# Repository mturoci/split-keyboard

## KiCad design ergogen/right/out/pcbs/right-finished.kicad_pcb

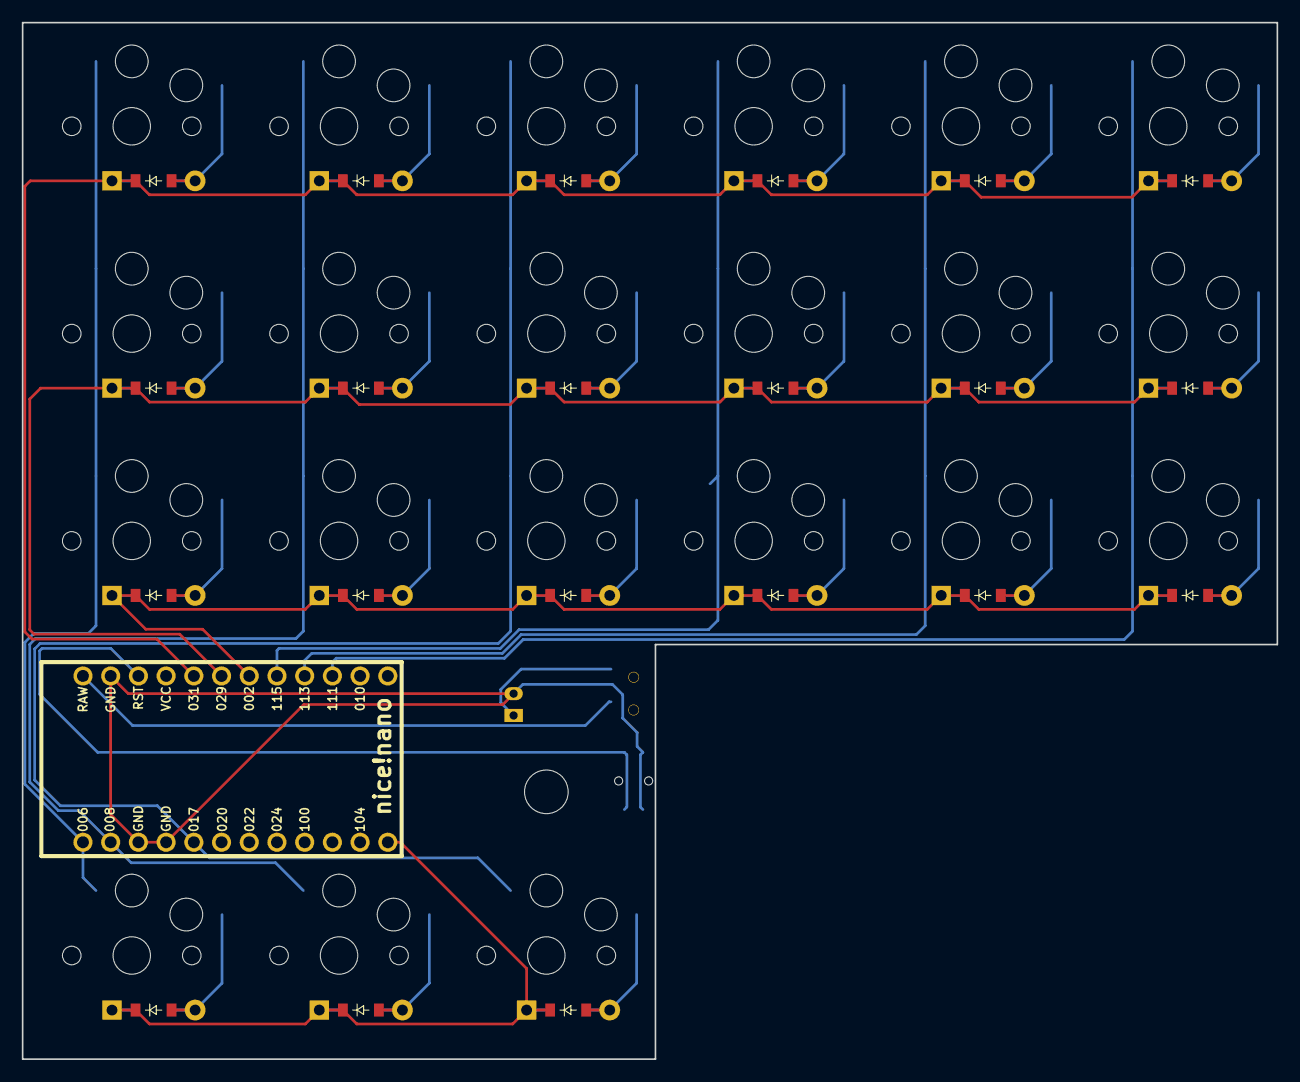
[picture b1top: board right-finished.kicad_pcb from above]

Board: 2 copper layers, 115.0 x 95.0 mm, 46 parts (0 on the bottom side), 35 nets.

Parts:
B1: Panasonic_EVQPUL_EVQPUC
D1, D2, D3, D4, D5, D6, D7, D8, D9, D10, D11, D12, D13, D14, D15, D16, D17, D18, D19, D20, D21: ComboDiode
JST1: JST_PH_S2B-PH-K_02x2.00mm_Angled
MCU1: nice_nano
S1, S2, S3, S4, S5, S6, S7, S8, S9, S10, S11, S12, S13, S14, S15, S16, S17, S18, S19, S20, S21: PG1350
T1: SPDT_C128955

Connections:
GND: B1.1, JST1.2, MCU1.3, MCU1.4, MCU1.23
P002: D2.1, D6.1, D10.1, D13.1, D16.1, D19.1, MCU1.18
P006: MCU1.1, S1.1, S2.1, S3.1, S4.1
P008: MCU1.2, S5.1, S6.1, S7.1, S8.1
P017: MCU1.5, S9.1, S10.1, S11.1, S12.1
P029: D3.1, D7.1, D11.1, D14.1, D17.1, D20.1, MCU1.19
P031: D4.1, D8.1, D12.1, D15.1, D18.1, D21.1, MCU1.20
P106: D1.1, D5.1, D9.1, MCU1.12
P111: MCU1.15, S19.1, S20.1, S21.1
P113: MCU1.16, S16.1, S17.1, S18.1
P115: MCU1.17, S13.1, S14.1, S15.1
RAW: MCU1.24, T1.2
RST: B1.2, MCU1.22
index_bottom: D6.2, S6.2
index_home: D7.2, S7.2
index_thumb: D5.2, S5.2
index_top: D8.2, S8.2
inner_bottom: D2.2, S2.2
inner_home: D3.2, S3.2
inner_thumb: D1.2, S1.2
inner_top: D4.2, S4.2
middle_bottom: D10.2, S10.2
middle_home: D11.2, S11.2
middle_thumb: D9.2, S9.2
middle_top: D12.2, S12.2
outer_bottom: D19.2, S19.2
outer_home: D20.2, S20.2
outer_top: D21.2, S21.2
pinky_bottom: D16.2, S16.2
pinky_home: D17.2, S17.2
pinky_top: D18.2, S18.2
pos: JST1.1, T1.1
ring_bottom: D13.2, S13.2
ring_home: D14.2, S14.2
ring_top: D15.2, S15.2

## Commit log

2025-09-23 feat: Initial tinkering.
2025-09-23 feat: Improved outline padding.
2025-09-23 feat: Move diodes a little bit.
2025-09-23 chore: Git ignore.
2025-09-23 feat: Shift nice nano to the empty row.
2025-09-23 feat: Add battery jack.
2025-09-23 feat: Add reset switch.
2025-09-24 feat: Add battery switch
2025-09-26 feat: Finished left side.
2025-09-26 feat: Shift PCB within KiCad
2025-09-26 chore: Split left and right.
2025-09-27 fix: Right part paddings.
2025-09-27 fix: MCU position
2025-09-27 fix: Buttons position
2025-09-27 feat: Add mounting hole to the left
2025-09-27 feat: Add mounting hole to the right.
2025-10-18 feat: Add zmk firmware. Default to corne.
2025-10-18 chore: Restructure.
2025-10-18 chore: Clean up.
2025-10-18 ci: Do not build on every push/pr.
2025-11-25 fix: Give Claude one more chance at fixing the wrong pins by creating a new shield.
2025-11-25 fix: Separate out row pins.
2025-11-25 fix: Reset settings when flashing.
2025-11-25 fix: Reverse rows.
2026-01-06 feat: Custom keymap.
2026-01-07 feat: Fill up custom keymap.
2026-01-07 fix: Tmp remap for testing.
2026-01-08 Revert "fix: Tmp remap for testing."
    This reverts commit ae162138c3391d4ef30f65b86912e4b3f203c945.
2026-01-08 feat: Add key repeat.
2026-01-08 feat: Add shift key support.
2026-01-09 feat: Change tap delay.
2026-01-09 feat: Add mouse movements.
2026-01-09 feat: Add brightness.
2026-01-09 fix: Syntax error.
2026-01-09 feat: Try to make mouse emulation work.
2026-01-09 feat: Actually push zmk pointing config.
2026-01-11 feat: Add more mouse binds.
2026-01-11 feat: Add 1 more layer.
2026-01-11 fix: Proper syntax.
2026-02-01 feat: Improve keymap.
2026-02-07 feat: Add forgotten backslash.
2026-02-16 fix: sync docs
